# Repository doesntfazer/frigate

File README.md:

# frigate
32/34 Key Keyboard, integrated rp2040

# Frigate V1 is not working. V2 is the final version of this keyboard.
Frigate V2 final are not the same as the Early adopter boards. This one has all of the silscreens, and it is also wired to support i2c and SPI versions of the cirque.
The early adopters version only supports SPI.

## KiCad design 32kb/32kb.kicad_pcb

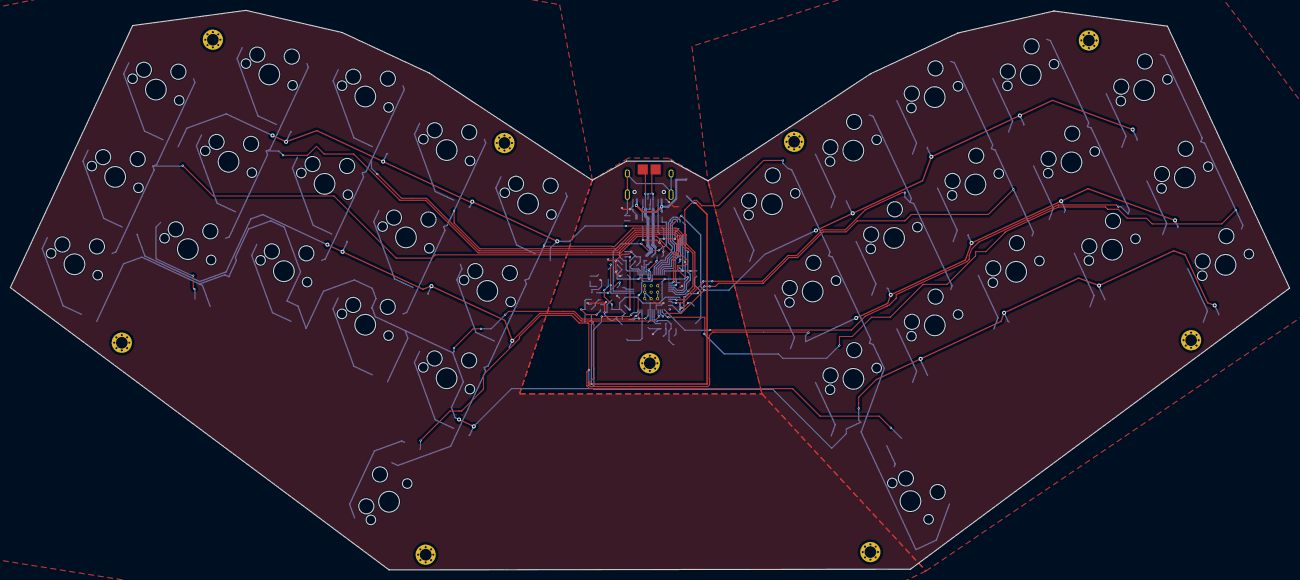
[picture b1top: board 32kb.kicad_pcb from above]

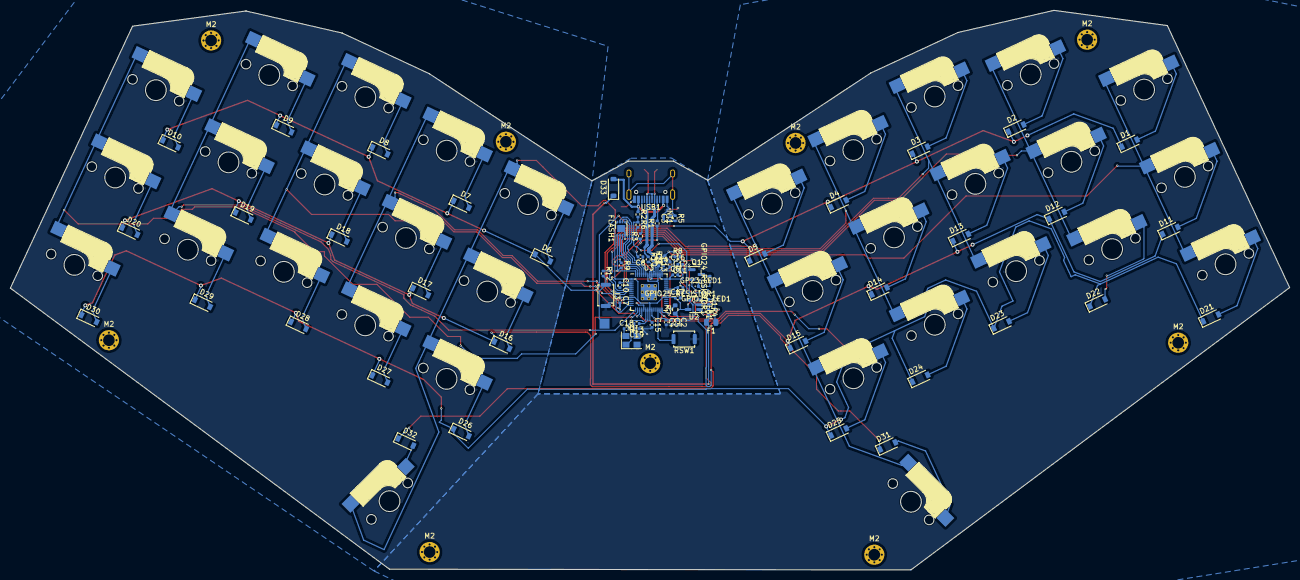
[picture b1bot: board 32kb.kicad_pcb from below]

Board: 2 copper layers, 252.9 x 110.6 mm, 124 parts (90 on the bottom side), 80 nets.

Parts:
C1, C2, C17: 10uf 0402; C_0402_1005Metric
C3: 0.1uf 0402; C_0402_1005Metric
C4, C5, C6, C7, C8, C9, C10, C11, C12, C15: 100nf 0402; C_0402_1005Metric
C13, C16: 2.2uF 0402; C_0402_1005Metric
C14: 1uf 0402; C_0402_1005Metric
C18, C19: 22pf 0402; C_0402_1005Metric
D1, D2, D3, D4, D5, D6, D7, D8, D9, D10, D11, D12, D13, D14, D15, D16, D17, D18, D19, D20, D21, D22, D23, D24, D25, D26, D27, D28, D29, D30, D31, D32: 1N4148W; D_SOD-123
D33: 1N4002W; D_SOD-123
F1: 0805L050WR; Fuse_0805_2012Metric
FB1: FerriteBead 0402; R_0402_1005Metric
FLASH1: W25Q16JVUXIQ; SON-8-1EP_3x2mm_P0.5mm_EP1.4x1.6mm
GP23_LED1: GP23 LED_0402; LED_0402_1005Metric
GPIO24_RESISTOR1: 1K 0402; R_0402_1005Metric
GPIO25_LED1: LED_0402; LED_0402_1005Metric
GPIO25_RESISTOR1: 470 0402; R_0402_1005Metric
J3: Button; SW_Push_SPST_NO_Alps_SKRK
M2, M2#2, M2#3, M2#4, M2#5, M2#6, M2#7, M2#8, M2#9: M2; M2_HOLE_v3
NT1: NetTie_2; NetTie-2_SMD_Pad0.5mm
Q1: SI2301B; SOT-23
R1, R3: 5.1K 0402; R_0402_1005Metric
R2: 5.6K 0402; R_0402_1005Metric
R4: 100K 0402; R_0402_1005Metric
R5: 220 0402; R_0402_1005Metric
R6, R9: 10K 0402; R_0402_1005Metric
R7: 200 0603; R_0603_1608Metric
R8: 1 0402; R_0402_1005Metric
R10, R11: 27r 0402 resistor; R_0402_1005Metric
R12, R13: 1K 0402; R_0402_1005Metric
RSW1: TSA343G00-250J2; SW_Push_SPST_NO_Alps_SKRK
SW1, SW2, SW3, SW4, SW5, SW6, SW7, SW8, SW9, SW10, SW11, SW12, SW13, SW14, SW15, SW16, SW17, SW18, SW19, SW20, SW21, SW22, SW23, SW24, SW25, SW26, SW27, SW28, SW29, SW30, SW31, SW32: SW_PUSH; CherryMX_Hotswap-3d-smd
TP1, TP2, TP3: TestPoint; CustomTestPoint
U2: SOT-23-5 5.5V 3.3V 500mA; SOT-23-5
U3: RP2040; RP2040-QFN-56
USB1: TYPE-C-31-M-12; HRO-TYPE-C-31-M-12
Y1: 3225_4P 12MHz; Crystal_SMD_3225-4Pin_3.2x2.5mm

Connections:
3V3_EN: R4.1, U2.3 (EN)
+1V1: C4.1, C5.1, C14.1, U3.23 (DVDD), U3.45 (VREG_VOUT), U3.50 (DVDD)
+3V3: C2.1, C6.1, C7.1, C8.1, C9.1, C10.1, C11.1, C12.1, C13.1, C15.1, C17.1, FLASH1.8 (VCC), Q1.2 (S), R7.1, R9.1, U2.5 (OUT), U3.1 (IOVDD), U3.10 (IOVDD), U3.22 (IOVDD), U3.33 (IOVDD), U3.42 (IOVDD), U3.44 (VREG_IN), U3.48 (USB_VDD), U3.49 (IOVDD)
/rp2040/ADC_VREF: R7.2, R8.1
/rp2040/GPIO23: Q1.1 (G), U3.35 (GPIO23)
/rp2040/GPIO24: R2.2, R6.1, U3.36 (GPIO24)
/rp2040/GPIO25: GPIO25_RESISTOR1.2, U3.37 (GPIO25)
/rp2040/QSPI_SCLK: FLASH1.6 (CLK), U3.52 (QSPI_SCLK)
/rp2040/QSPI_SD0: FLASH1.5 (DI(IO0)), U3.53 (QSPI_SD0)
/rp2040/QSPI_SD1: FLASH1.2 (DO(IO1)), U3.55 (QSPI_SD1)
/rp2040/QSPI_SD2: FLASH1.3 (IO2), U3.54 (QSPI_SD2)
/rp2040/QSPI_SD3: FLASH1.7 (IO3), U3.51 (QSPI_SD3)
/rp2040/QSPI_SS: FLASH1.1 (~CS), R9.2, R12.1, U3.56 (QSPI_SS)
/rp2040/RUN: RSW1.2, U3.26 (RUN)
/rp2040/~USB_BOOT: J3.1, R12.2, TP3.1
COL0: SW1.2, SW11.2, SW21.2, U3.3 (GPIO1)
COL1: SW2.2, SW12.2, SW22.2, U3.4 (GPIO2)
COL2: SW3.2, SW13.2, SW23.2, U3.5 (GPIO3)
COL3: SW4.2, SW14.2, SW24.2, U3.6 (GPIO4)
COL4: SW5.2, SW15.2, SW25.2, SW31.2, U3.7 (GPIO5)
COL5: SW6.2, SW16.2, SW26.2, SW32.2, U3.11 (GPIO8)
COL6: SW7.2, SW17.2, SW27.2, U3.12 (GPIO9)
COL7: SW8.2, SW18.2, SW28.2, U3.14 (GPIO11)
COL8: SW9.2, SW19.2, SW29.2, U3.15 (GPIO12)
COL9: SW10.2, SW20.2, SW30.2, U3.16 (GPIO13)
GND: C1.2, C2.2, C3.1, C4.2, C5.2, C6.2, C7.2, C8.2, C9.2, C10.2, C11.2, C12.2, C13.2, C14.2, C15.2, C16.2, C17.2, C18.1, C19.1, FLASH1.4 (GND), FLASH1.9 (EP), GP23_LED1.1 (K), GPIO25_LED1.1 (K), J3.2, NT1.1, R1.1, R3.1, R5.2, R6.2, RSW1.1, U2.2 (GND), U2.4 (BP), U3.19 (TESTEN), U3.57 (GND), USB1.1 (GND), USB1.12 (GND), Y1.2, Y1.4
unnamed: C19.2, R13.2, Y1.3
unnamed: D1.2 (A), SW1.1
unnamed: D2.2 (A), SW2.1
unnamed: D3.2 (A), SW3.1
unnamed: D4.2 (A), SW4.1
unnamed: D5.2 (A), SW5.1
unnamed: D6.2 (A), SW6.1
unnamed: D7.2 (A), SW7.1
unnamed: D8.2 (A), SW8.1
unnamed: D9.2 (A), SW9.1
unnamed: D10.2 (A), SW10.1
unnamed: D11.2 (A), SW11.1
unnamed: D12.2 (A), SW12.1
unnamed: D13.2 (A), SW13.1
unnamed: D14.2 (A), SW14.1
unnamed: D15.2 (A), SW15.1
unnamed: D16.2 (A), SW16.1
unnamed: D17.2 (A), SW17.1
unnamed: D18.2 (A), SW18.1
unnamed: D19.2 (A), SW19.1
unnamed: D20.2 (A), SW20.1
unnamed: D21.2 (A), SW21.1
unnamed: D22.2 (A), SW22.1
unnamed: D23.2 (A), SW23.1
unnamed: D24.2 (A), SW24.1
unnamed: D25.2 (A), SW25.1
unnamed: D26.2 (A), SW26.1
unnamed: D27.2 (A), SW27.1
unnamed: D28.2 (A), SW28.1
unnamed: D29.2 (A), SW29.1
unnamed: D30.2 (A), SW30.1
unnamed: D31.2 (A), SW31.1
unnamed: D32.2 (A), SW32.1
unnamed: F1.1, FB1.1
unnamed: GP23_LED1.2 (A), GPIO24_RESISTOR1.1
unnamed: GPIO25_LED1.2 (A), GPIO25_RESISTOR1.1
unnamed: GPIO24_RESISTOR1.2, Q1.3 (D)
unnamed: C1.1, FB1.2, U2.1 (IN)
unnamed: C16.1, R8.2, U3.43 (ADC_AVDD)
unnamed: R11.2, U3.46 (USB_DM)
unnamed: R10.2, U3.47 (USB_DP)
unnamed: R1.2, USB1.4 (CC1)
unnamed: R3.2, USB1.10 (CC2)
unnamed: C3.2, R5.1, USB1.13 (SHIELD)
ROW0: D1.1 (K), D2.1 (K), D3.1 (K), D4.1 (K), D5.1 (K), D6.1 (K), D7.1 (K), D8.1 (K), D9.1 (K), D10.1 (K), U3.17 (GPIO14)
ROW1: D11.1 (K), D12.1 (K), D13.1 (K), D14.1 (K), D15.1 (K), D16.1 (K), D17.1 (K), D18.1 (K), D19.1 (K), D20.1 (K), U3.18 (GPIO15)
ROW2: D21.1 (K), D22.1 (K), D23.1 (K), D24.1 (K), D25.1 (K), D26.1 (K), D27.1 (K), D28.1 (K), D29.1 (K), D30.1 (K), U3.27 (GPIO16)
ROW3: D31.1 (K), D32.1 (K), U3.28 (GPIO17)
USB_D+: R10.1, TP1.1, USB1.6 (DP1), USB1.8 (DP2)
USB_D-: R11.1, TP2.1, USB1.5 (DN2), USB1.7 (DN1)
VBUS: D33.2 (A), R2.1, USB1.2 (VBUS), USB1.11 (VBUS)
VSYS: D33.1 (K), F1.2, R4.2
XIN: C18.2, U3.20 (XIN), Y1.1
XOUT: R13.1, U3.21 (XOUT)

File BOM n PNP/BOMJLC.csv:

Comment,Designator,Footprint,LCSC Part #
10uf 0402,"C1, C2, C17",C_0402_1005Metric,no_part_number
0.1uf 0402,C3,C_0402_1005Metric,no_part_number
100nf 0402,"C4, C5, C6, C7, C8, C9, C10, C11, C12, C15",C_0402_1005Metric,no_part_number
2.2uF 0402,"C13, C16",C_0402_1005Metric,no_part_number
1uf 0402,C14,C_0402_1005Metric,no_part_number
22pf 0402,"C18, C19",C_0402_1005Metric,no_part_number
,,,
1N4148W,"D1, D2, D3, D4, D5, D6, D7, D8, D9, D10, D11, D12, D13, D14, D15, D16, D17, D18, D19, D20, D21, D22, D23, D24, D25, D26, D27, D28, D29, D30, D31, D32",D_SOD-123,C2892570
1N4002W,D33,D_SOD-123,C169542
0805L050WR,F1,Fuse_0805_2012Metric,C207022
FerriteBead 0402,FB1,R_0402_1005Metric,no_part_number
W25Q16JVUXIQ,FLASH1,R_0402_1005Metric,C2843335
GP23 LED_0402,GP23_LED1,LED_0402_1005Metric,no_part_number
1K 0402,GPIO24_RESISTOR1,R_0402_1005Metric,no_part_number
LED_0402,GPIO25_LED1,LED_0402_1005Metric,no_part_number
470 0402,GPIO25_RESISTOR1,R_0402_1005Metric,no_part_number
Button,J3,SW_Push_SPST_NO_Alps_SKRK,no_part_number
NetTie_2,NT1,NetTie-2_SMD_Pad0.5mm,no_part_number
SI2301B, Q1,SOT-23,no_part_number
5.1K 0402,"R1, R3",R_0402_1005Metric,no_part_number
5.6K 0402,R2,R_0402_1005Metric,no_part_number
100K 0402,R4,R_0402_1005Metric,no_part_number
220 0402,R5,R_0402_1005Metric,no_part_number
10K 0402,"R6, R9",R_0402_1005Metric,no_part_number
200 0603,R7,R_0402_1005Metric,no_part_number
1 0402,R8,R_0402_1005Metric,no_part_number
27r 0402 resistor,"R10, R11",R_0402_1005Metric,no_part_number
1K 0402,"R12, R13",R_0402_1005Metric,no_part_number
TSA343G00-250J2,RSW1,SW_Push_SPST_NO_Alps_SKRK,C354946
SW_PUSH,SW1-SW32,CherryMX_Hotswap-3d-smd,C5156480
TestPoint,"TP1, TP2, TP3",CustomTestPoint,no_part_number
SOT-23-5 5.5V 3.3V 500mA,U2,SOT-23-5,C404027
RP2040,U3,RP2040-QFN-56, C2040
TYPE-C-31-M-12,USB1,HRO-TYPE-C-31-M-12,C165948
3225_4P 12MHz,Y1,Crystal_SMD_3225-4Pin_3.2x2.5mm,C295522

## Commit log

2023-04-11 initial
2023-04-12 Added more components and stuff for later revisions
2023-05-12 Added V2 final renamed v1
2023-05-12 Moving stuff around
